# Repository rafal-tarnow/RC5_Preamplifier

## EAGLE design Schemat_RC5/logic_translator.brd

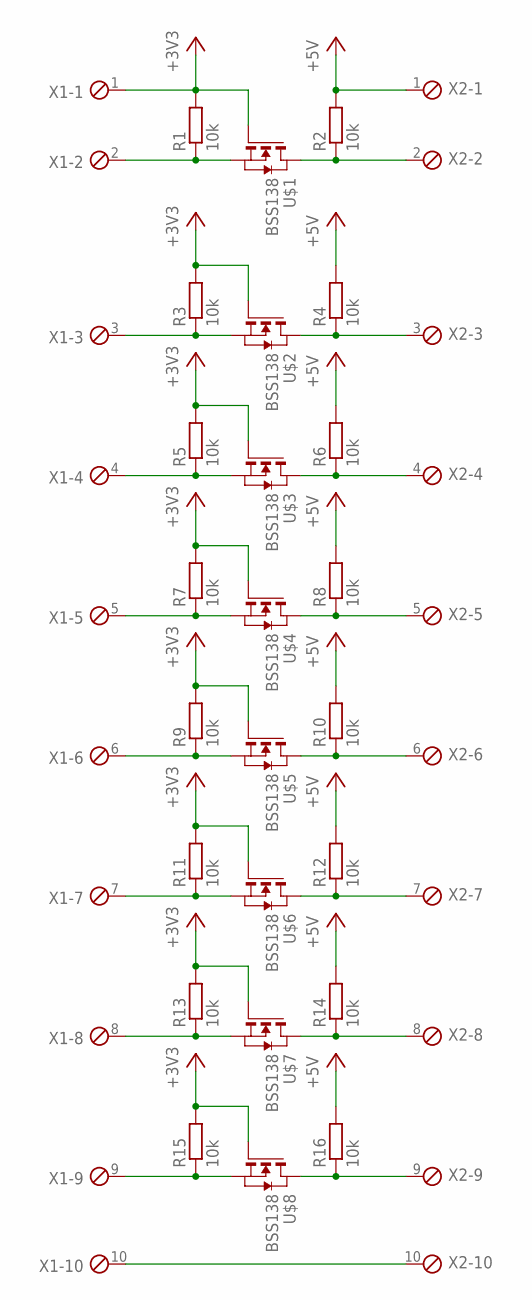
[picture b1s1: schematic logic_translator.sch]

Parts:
R1, R2, R3, R4, R5, R6, R7, R8, R9, R10, R11, R12, R13, R14, R15, R16: 10k; R1206
U$1, U$2, U$3, U$4, U$5, U$6, U$7, U$8: BSS138; SOT-23
X1, X2: MPT10; 10POL254

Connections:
+3V3: R1.2, R3.2, R5.2, R7.2, R9.2, R11.2, R13.2, R15.2, U$1.3 (G), U$2.3 (G), U$3.3 (G), U$4.3 (G), U$5.3 (G), U$6.3 (G), U$7.3 (G), U$8.3 (G), X1.1
+5V: R2.2, R4.2, R6.2, R8.2, R10.2, R12.2, R14.2, R16.2, X2.1
unnamed: R1.1, U$1.2 (S), X1.2
unnamed: R3.1, U$2.2 (S), X1.3
unnamed: R2.1, U$1.1 (D), X2.2
unnamed: R4.1, U$2.1 (D), X2.3
unnamed: R5.1, U$3.2 (S), X1.4
unnamed: R6.1, U$3.1 (D), X2.4
unnamed: R7.1, U$4.2 (S), X1.5
unnamed: R8.1, U$4.1 (D), X2.5
unnamed: R9.1, U$5.2 (S), X1.6
unnamed: R10.1, U$5.1 (D), X2.6
unnamed: R11.1, U$6.2 (S), X1.7
unnamed: R12.1, U$6.1 (D), X2.7
unnamed: R13.1, U$7.2 (S), X1.8
unnamed: R14.1, U$7.1 (D), X2.8
unnamed: R15.1, U$8.2 (S), X1.9
unnamed: R16.1, U$8.1 (D), X2.9
unnamed: X1.10, X2.10

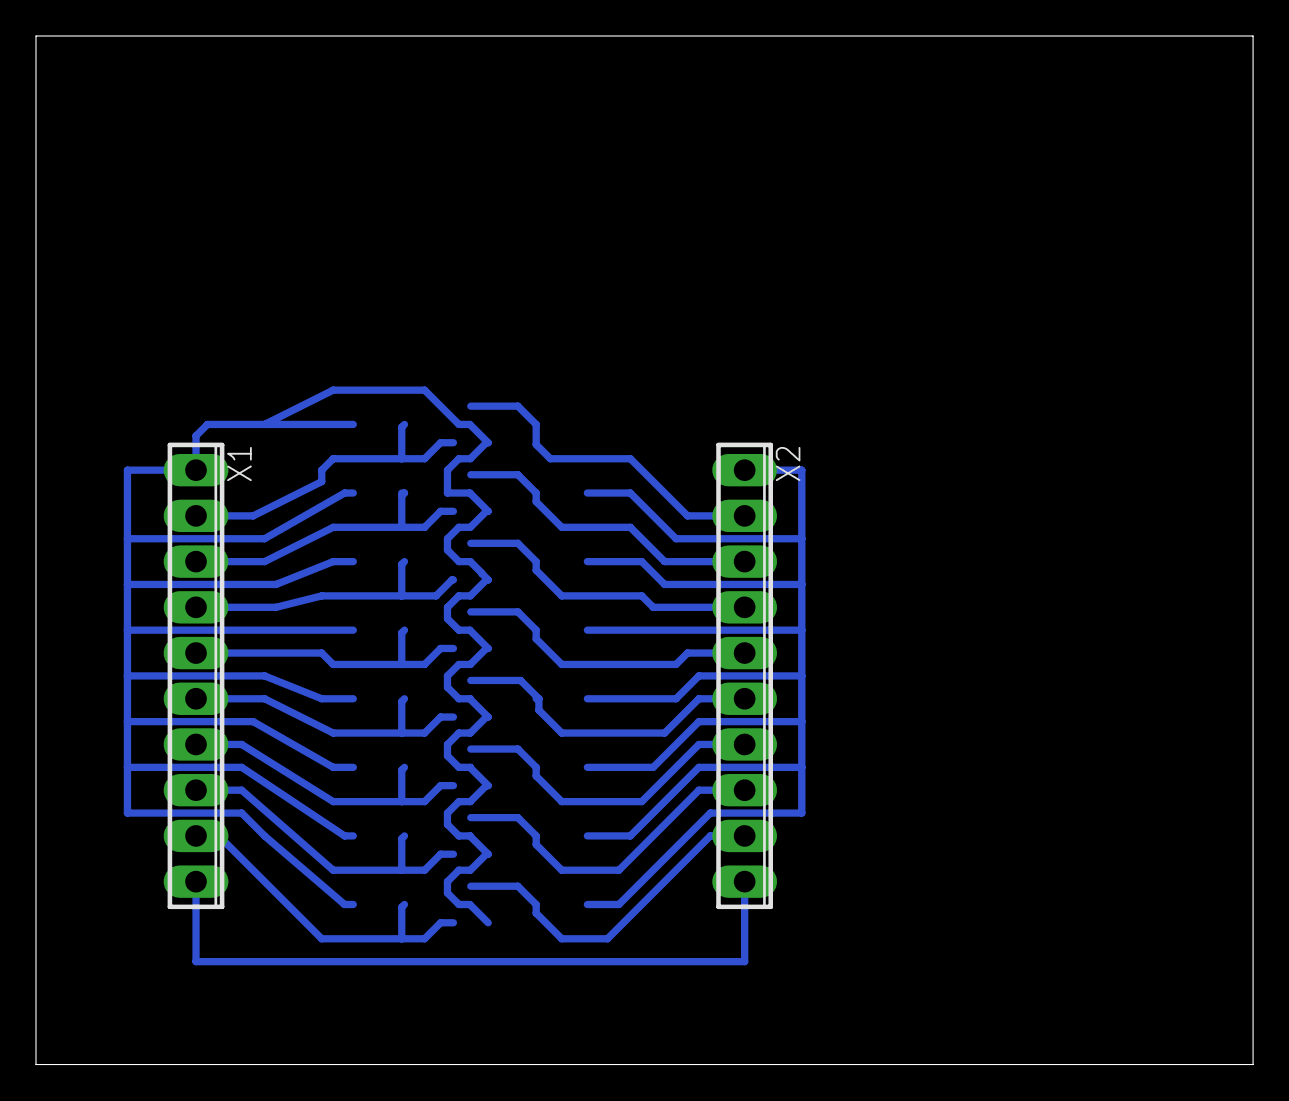
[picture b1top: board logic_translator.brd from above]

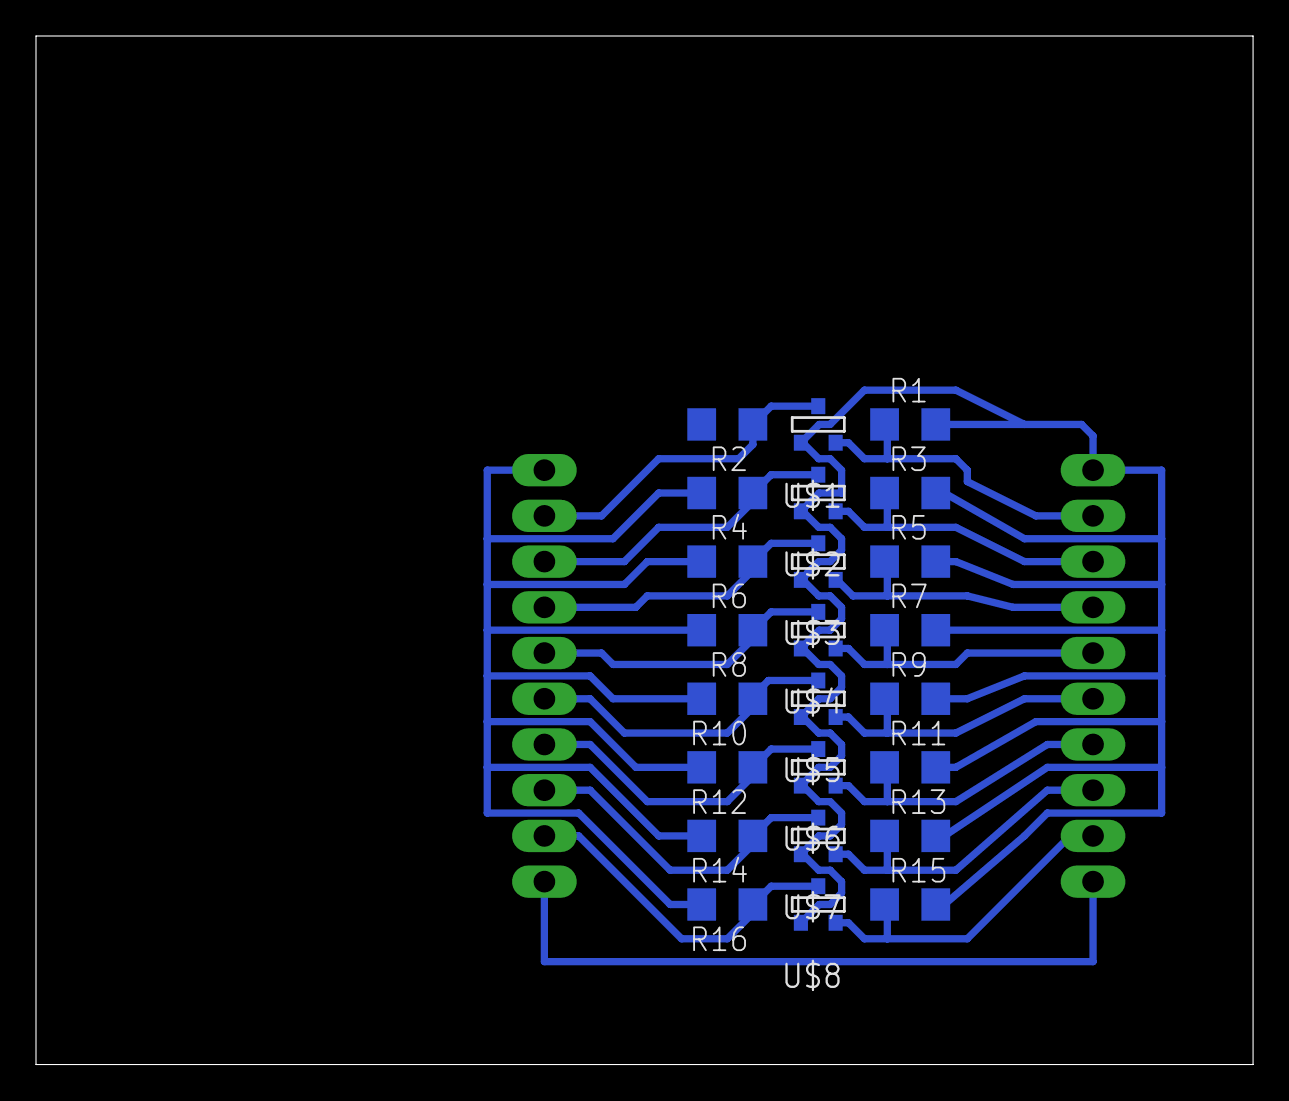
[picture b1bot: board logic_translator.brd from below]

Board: 2 copper layers, 67.6 x 57.1 mm, 26 parts (24 on the bottom side), 19 nets.

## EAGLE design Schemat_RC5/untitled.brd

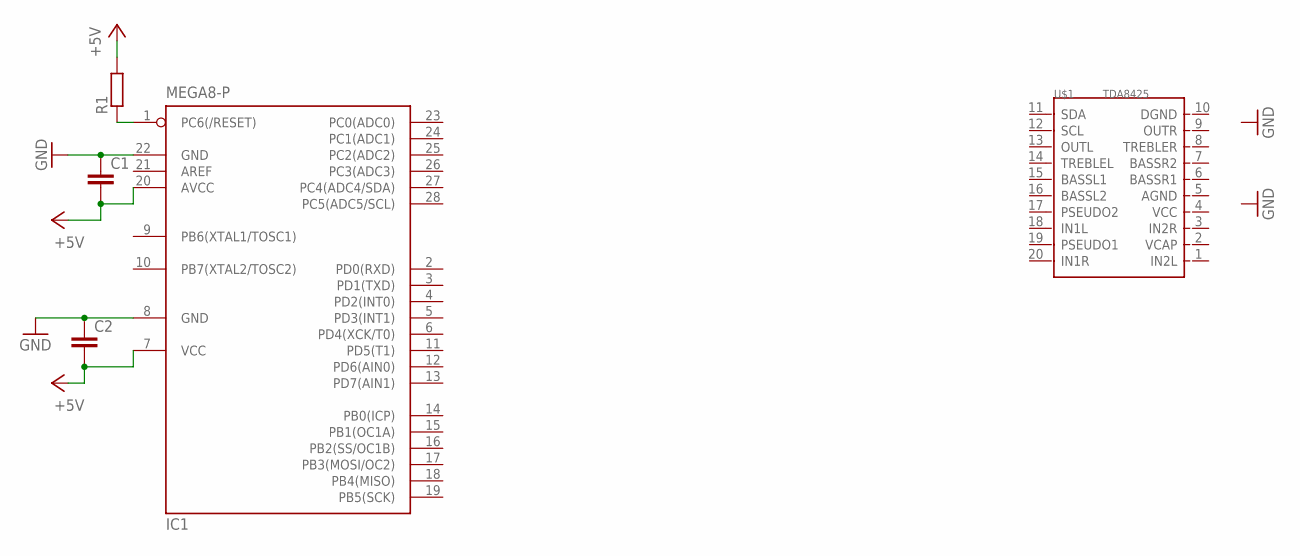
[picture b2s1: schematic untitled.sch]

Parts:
C1, C2: C-EUC0805; C0805
IC1: MEGA8-P; DIL28-3
R1: R-EU_R0805; R0805
U$1: TDA8425; DIP20-2.54-26.2X7.62MM

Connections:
+5V: C1.2, C2.2, IC1.7 (VCC), IC1.20 (AVCC), R1.2
GND: C1.1, C2.1, IC1.8 (GND), IC1.22 (GND)
unnamed: IC1.1 (PC6(/RESET)), R1.1

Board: 2 copper layers, 5 parts (0 on the bottom side), 3 nets, no tracks yet.

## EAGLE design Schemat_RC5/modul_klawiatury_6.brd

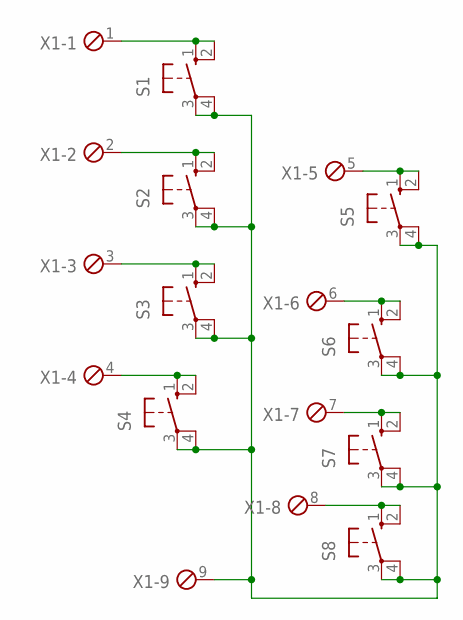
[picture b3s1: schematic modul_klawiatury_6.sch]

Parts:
S1, S2, S3, S4, S5, S6, S7, S8: 10-XX; B3F-10XX
X1: MPT9; 9POL254

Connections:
unnamed: S1.1 (S), S1.2 (S1), X1.1
unnamed: S2.1 (S), S2.2 (S1), X1.2
unnamed: S3.1 (S), S3.2 (S1), X1.3
unnamed: S4.1 (S), S4.2 (S1), X1.4
unnamed: S5.1 (S), S5.2 (S1), X1.5
unnamed: S6.1 (S), S6.2 (S1), X1.6
unnamed: S8.1 (S), S8.2 (S1), X1.8
unnamed: S7.1 (S), S7.2 (S1), X1.7
unnamed: S1.3, S1.4 (P1), S2.3, S2.4 (P1), S3.3, S3.4 (P1), S4.3, S4.4 (P1), S5.3, S5.4 (P1), S6.3, S6.4 (P1), S7.3, S7.4 (P1), S8.3, S8.4 (P1), X1.9

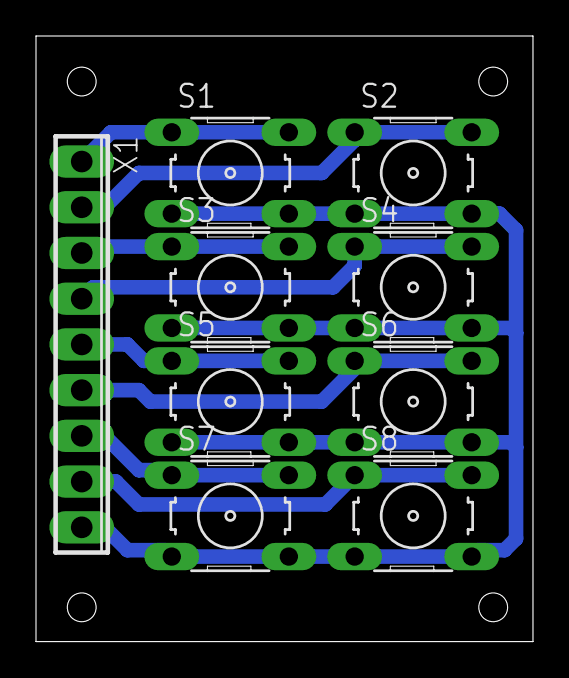
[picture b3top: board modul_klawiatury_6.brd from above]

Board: 2 copper layers, 27.6 x 33.6 mm, 9 parts (0 on the bottom side), 9 nets.

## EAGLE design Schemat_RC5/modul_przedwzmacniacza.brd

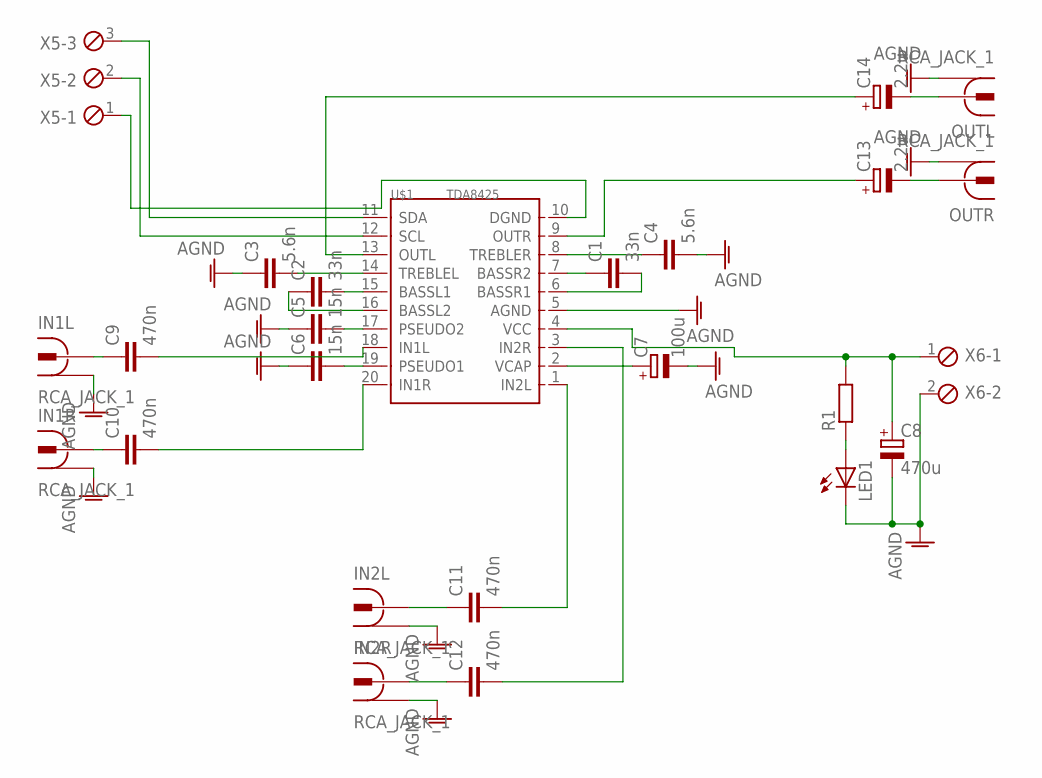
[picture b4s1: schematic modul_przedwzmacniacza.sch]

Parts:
C1, C2: 33n; C050-025X075
C3, C4: 5.6n; C050-030X075
C5, C6: 15n; C050-025X075
C7: 100u; E2,5-6
C8: 470u; E3,5-8
C9, C10, C11, C12: 470n; C050-045X075
C13, C14: 2.2u; E2-4
IN1L, IN1R, IN2L, IN2R: RCA_JACK_1; 736880-50
LED1: LED3MM
OUTL: RCA_JACK_1; 736880-50
OUTR: RCA_JACK_1; 736880-50
R1: R-EU_R1206; R1206
U$1: TDA8425; DIP20-2.54-26.2X7.62MM
X5: MPT3; 3POL254
X6: MPT2; 2POL254

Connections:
AGND: C3.1, C4.2, C5.1, C6.1, C7.-, C8.-, IN1L.1, IN1R.1, IN2L.1, IN2R.1, LED1.K (C), OUTL.1, OUTR.1, U$1.5 (AGND), X6.2
DGND: U$1.10 (DGND), X5.1
IN2R: C12.2, U$1.3 (IN2R)
unnamed: C11.2, U$1.1 (IN2L)
unnamed: C9.2, U$1.18 (IN1L)
unnamed: C10.2, U$1.20 (IN1R)
unnamed: C9.1, IN1L.2
unnamed: C10.1, IN1R.2
unnamed: C11.1, IN2L.2
unnamed: C1.1, U$1.7 (BASSR2)
unnamed: C1.2, U$1.6 (BASSR1)
unnamed: C2.2, U$1.15 (BASSL1)
unnamed: C2.1, U$1.16 (BASSL2)
unnamed: C3.2, U$1.14 (TREBLEL)
unnamed: C4.1, U$1.8 (TREBLER)
unnamed: C5.2, U$1.17 (PSEUDO2)
unnamed: C6.2, U$1.19 (PSEUDO1)
unnamed: C7.+, U$1.2 (VCAP)
unnamed: C12.1, IN2R.2
unnamed: C13.+, U$1.9 (OUTR)
unnamed: C13.-, OUTR.2
unnamed: C14.-, OUTL.2
unnamed: LED1.A, R1.1
OUTL: C14.+, U$1.13 (OUTL)
SCL: U$1.12 (SCL), X5.2
SDA: U$1.11 (SDA), X5.3
VCC: C8.+, R1.2, U$1.4 (VCC), X6.1

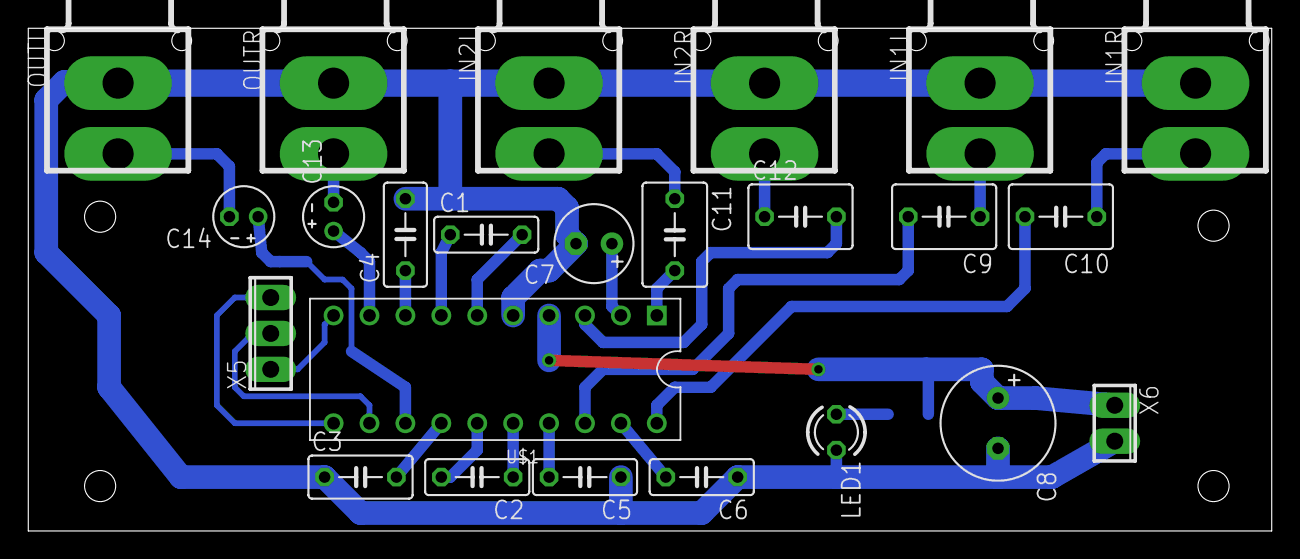
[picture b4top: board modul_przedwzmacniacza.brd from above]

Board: 2 copper layers, 87.9 x 35.5 mm, 25 parts (1 on the bottom side), 27 nets.

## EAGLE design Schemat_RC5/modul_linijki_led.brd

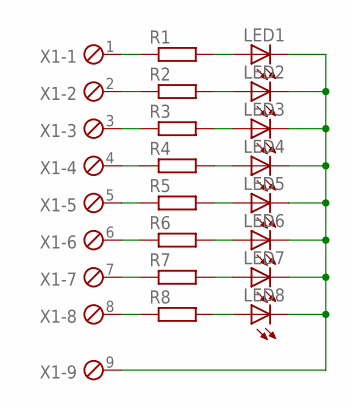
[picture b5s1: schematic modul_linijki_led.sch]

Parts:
LED1, LED2, LED3, LED4, LED5, LED6, LED7, LED8: LED3MM
R1, R2, R3, R4, R5, R6, R7, R8: R-EU_R0805; R0805
X1: MPT9; 9POL254

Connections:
unnamed: LED1.A, R1.2
unnamed: LED2.A, R2.2
unnamed: LED3.A, R3.2
unnamed: LED4.A, R4.2
unnamed: LED5.A, R5.2
unnamed: LED6.A, R6.2
unnamed: LED7.A, R7.2
unnamed: LED8.A, R8.2
unnamed: LED1.K (C), LED2.K (C), LED3.K (C), LED4.K (C), LED5.K (C), LED6.K (C), LED7.K (C), LED8.K (C), X1.9
unnamed: R1.1, X1.1
unnamed: R2.1, X1.2
unnamed: R3.1, X1.3
unnamed: R4.1, X1.4
unnamed: R5.1, X1.5
unnamed: R6.1, X1.6
unnamed: R7.1, X1.7
unnamed: R8.1, X1.8

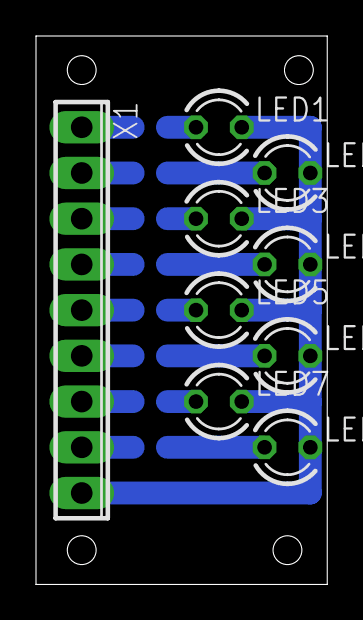
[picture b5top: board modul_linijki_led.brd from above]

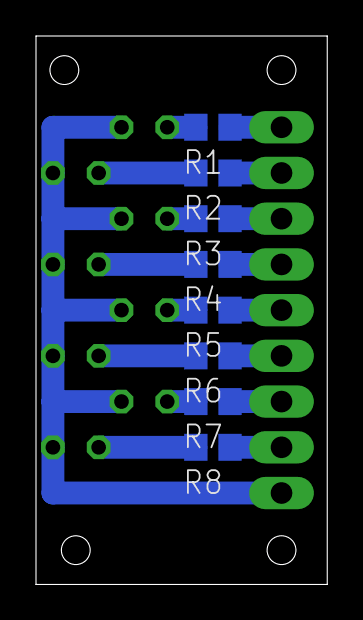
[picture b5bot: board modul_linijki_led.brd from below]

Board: 2 copper layers, 16.2 x 30.5 mm, 17 parts (8 on the bottom side), 17 nets.

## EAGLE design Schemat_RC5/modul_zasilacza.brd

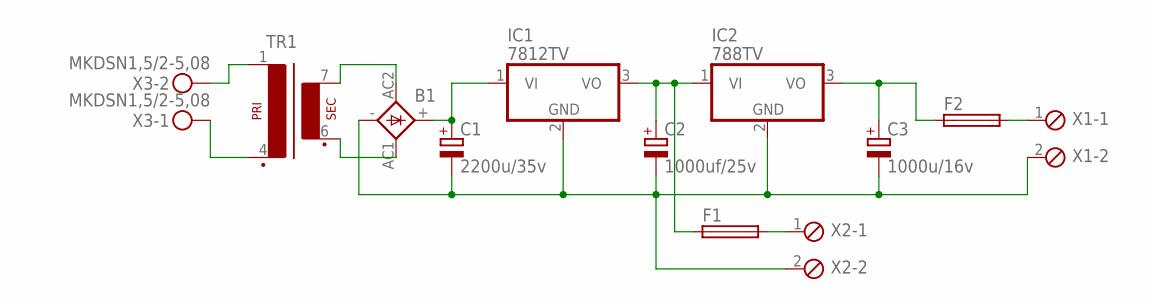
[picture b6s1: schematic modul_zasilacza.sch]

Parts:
B1: KBL
C1: 2200u/35v; E3,5-8
C2: 1000uf/25v; E3,5-8
C3: 1000u/16v; E3,5-8
F1, F2: GSH15
IC1: 7812TV; TO220V
IC2: 788TV; TO220V
TR1: EE20-1
X1, X2: MPT2; 2POL254
X3: MKDSN1,5/2-5,08

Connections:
unnamed: B1.+, C1.+, IC1.1 (VI)
unnamed: B1.AC1 (AC2), TR1.6 (S3)
unnamed: B1.AC2 (AC1), TR1.7 (S4)
unnamed: B1.-, C1.-, C2.-, C3.-, IC1.2 (GND), IC2.2 (GND), X1.2, X2.2
unnamed: C2.+, F1.1, IC1.3 (VO), IC2.1 (VI)
unnamed: F1.2, X2.1
unnamed: C3.+, F2.1, IC2.3 (VO)
unnamed: F2.2, X1.1
unnamed: TR1.1, X3.2
unnamed: TR1.4 (P2), X3.1

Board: 2 copper layers, 12 parts (0 on the bottom side), 10 nets, no tracks yet.

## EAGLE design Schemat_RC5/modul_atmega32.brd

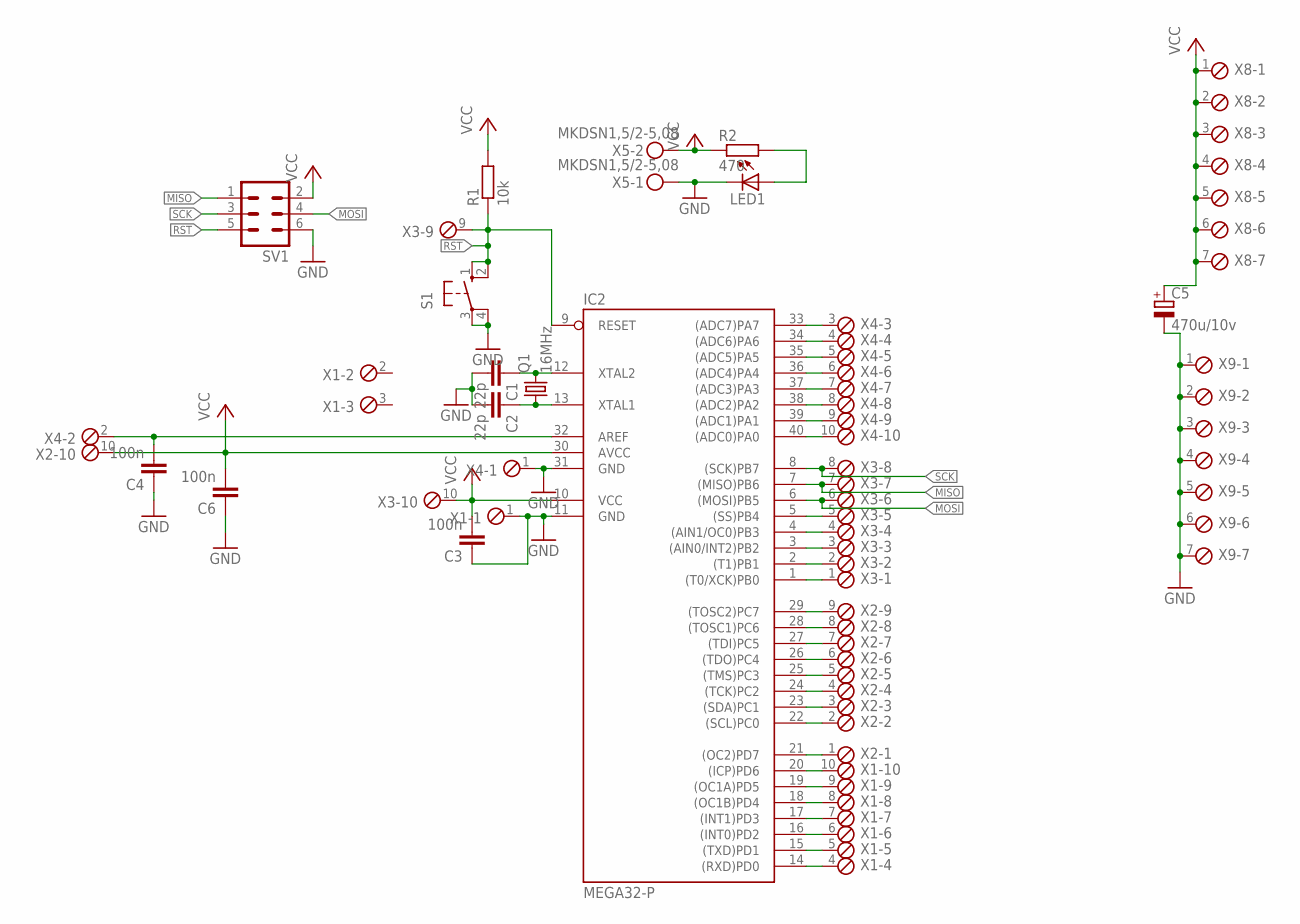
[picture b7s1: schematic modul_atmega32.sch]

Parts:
C1, C2: 22p; C0805K
C3, C4, C6: 100n; C1206
C5: 470u/10v; E5-8,5
IC2: MEGA32-P; DIL40
LED1: LED3MM
Q1: 16MHz; HC49UP
R1: 10k; R1206
R2: 470; R1206
S1: 10-XX; B3F-10XX
SV1: MA03-2
X1, X2, X3, X4: MPT10; 10POL254
X5: MKDSN1,5/2-5,08
X8, X9: MPT7; 7POL254

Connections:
AREF: C4.2, IC2.32 (AREF), X4.2
GND: C1.2, C2.2, C3.1, C4.1, C5.-, C6.1, IC2.11 (GND), IC2.31 (GND), LED1.K (C), S1.3, S1.4 (P1), SV1.6, X1.1, X4.1, X5.1, X9.1, X9.2, X9.3, X9.4, X9.5, X9.6, X9.7
MISO: IC2.7 ((MISO)PB6), SV1.1, X3.7
MOSI: IC2.6 ((MOSI)PB5), SV1.4, X3.6
unnamed: IC2.21 ((OC2)PD7), X2.1
unnamed: LED1.A, R2.2
unnamed: IC2.5 ((SS)PB4), X3.5
unnamed: IC2.4 ((AIN1/OC0)PB3), X3.4
unnamed: IC2.3 ((AIN0/INT2)PB2), X3.3
unnamed: IC2.2 ((T1)PB1), X3.2
unnamed: IC2.1 ((T0/XCK)PB0), X3.1
unnamed: IC2.14 ((RXD)PD0), X1.4
unnamed: IC2.15 ((TXD)PD1), X1.5
unnamed: IC2.16 ((INT0)PD2), X1.6
unnamed: IC2.17 ((INT1)PD3), X1.7
unnamed: IC2.18 ((OC1B)PD4), X1.8
unnamed: IC2.19 ((OC1A)PD5), X1.9
unnamed: IC2.20 ((ICP)PD6), X1.10
unnamed: C2.1, IC2.13 (XTAL1), Q1.1
unnamed: C1.1, IC2.12 (XTAL2), Q1.2
unnamed: IC2.29 ((TOSC2)PC7), X2.9
unnamed: IC2.28 ((TOSC1)PC6), X2.8
unnamed: IC2.27 ((TDI)PC5), X2.7
unnamed: IC2.26 ((TDO)PC4), X2.6
unnamed: IC2.25 ((TMS)PC3), X2.5
unnamed: IC2.24 ((TCK)PC2), X2.4
unnamed: IC2.23 ((SDA)PC1), X2.3
unnamed: IC2.22 ((SCL)PC0), X2.2
unnamed: IC2.33 ((ADC7)PA7), X4.3
unnamed: IC2.34 ((ADC6)PA6), X4.4
unnamed: IC2.35 ((ADC5)PA5), X4.5
unnamed: IC2.36 ((ADC4)PA4), X4.6
unnamed: IC2.37 ((ADC3)PA3), X4.7
unnamed: IC2.38 ((ADC2)PA2), X4.8
unnamed: IC2.39 ((ADC1)PA1), X4.9
unnamed: IC2.40 ((ADC0)PA0), X4.10
RST: IC2.9 (RESET), R1.1, S1.1 (S), S1.2 (S1), SV1.5, X3.9
SCK: IC2.8 ((SCK)PB7), SV1.3, X3.8
VCC: C3.2, C5.+, C6.2, IC2.10 (VCC), IC2.30 (AVCC), R1.2, R2.1, SV1.2, X2.10, X3.10, X5.2, X8.1, X8.2, X8.3, X8.4, X8.5, X8.6, X8.7

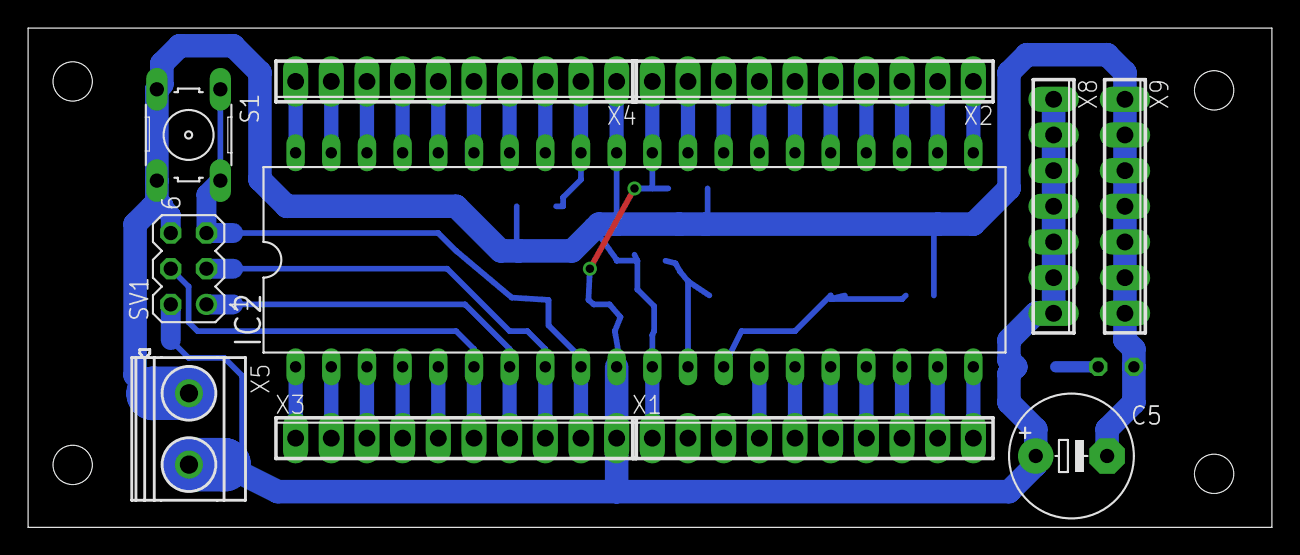
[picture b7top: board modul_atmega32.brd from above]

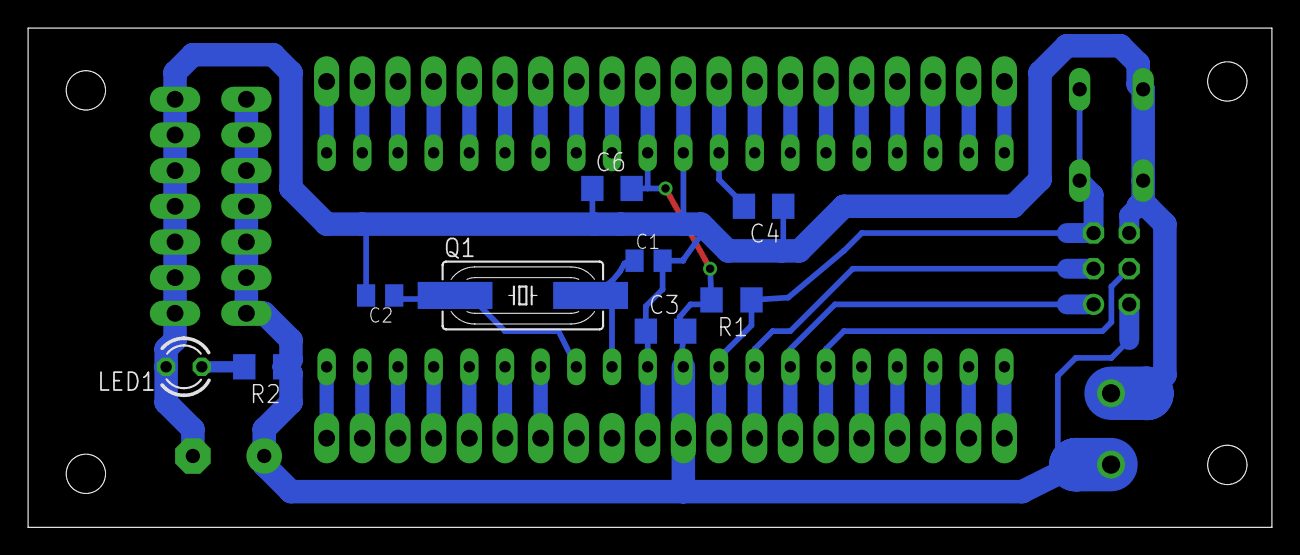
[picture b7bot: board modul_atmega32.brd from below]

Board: 2 copper layers, 88.6 x 35.5 mm, 20 parts (9 on the bottom side), 39 nets.

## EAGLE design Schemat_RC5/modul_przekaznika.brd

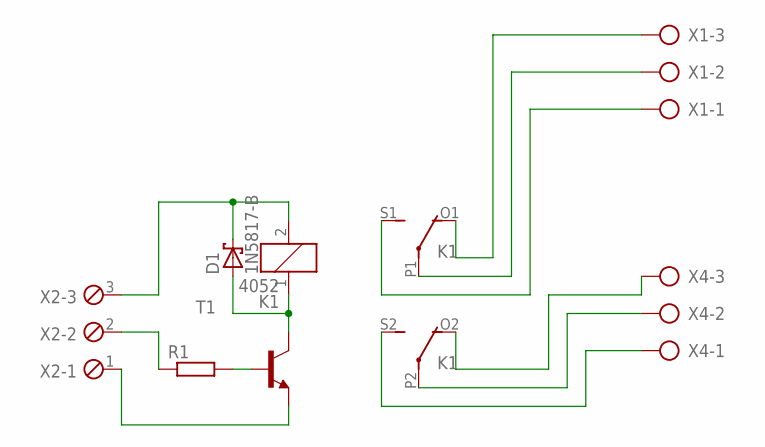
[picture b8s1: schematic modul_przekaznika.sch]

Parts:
D1: 1N5817-B; DO41-7.6
K1: 4052; F4052
R1: R-EU_M1206; M1206
T1: BC548-NPN-TO92-CBE; TO92-CBE
X1, X4: AK500/3
X2: MPT3; 3POL254

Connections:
unnamed: D1.A, K1.1, T1.C
unnamed: D1.C, K1.2, X2.3
unnamed: K1.S2 (S), X4.1
unnamed: K1.P2, X4.2
unnamed: K1.O2 (O), X4.3
unnamed: K1.S1 (S), X1.1
unnamed: K1.P1, X1.2
unnamed: K1.O1 (O), X1.3
unnamed: T1.E, X2.1
unnamed: R1.1, X2.2
unnamed: R1.2, T1.B

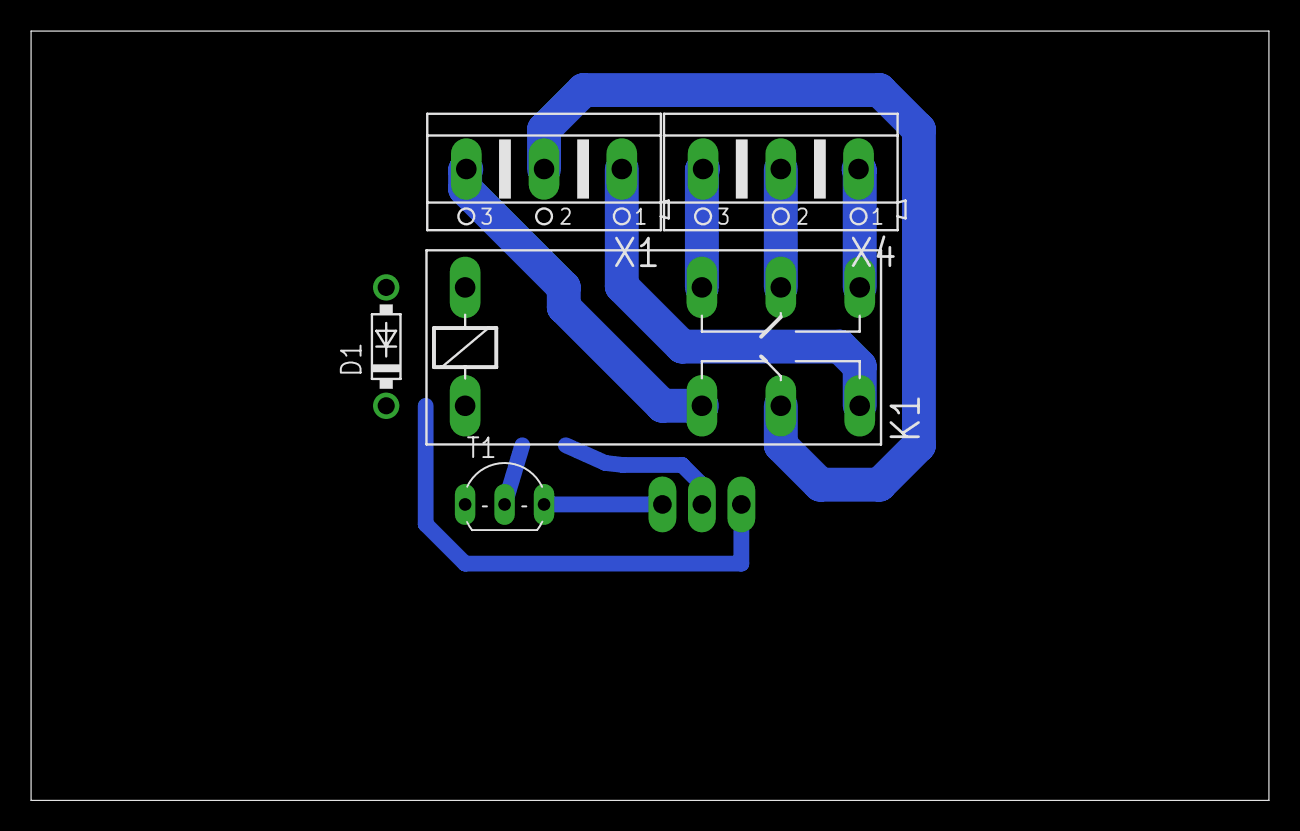
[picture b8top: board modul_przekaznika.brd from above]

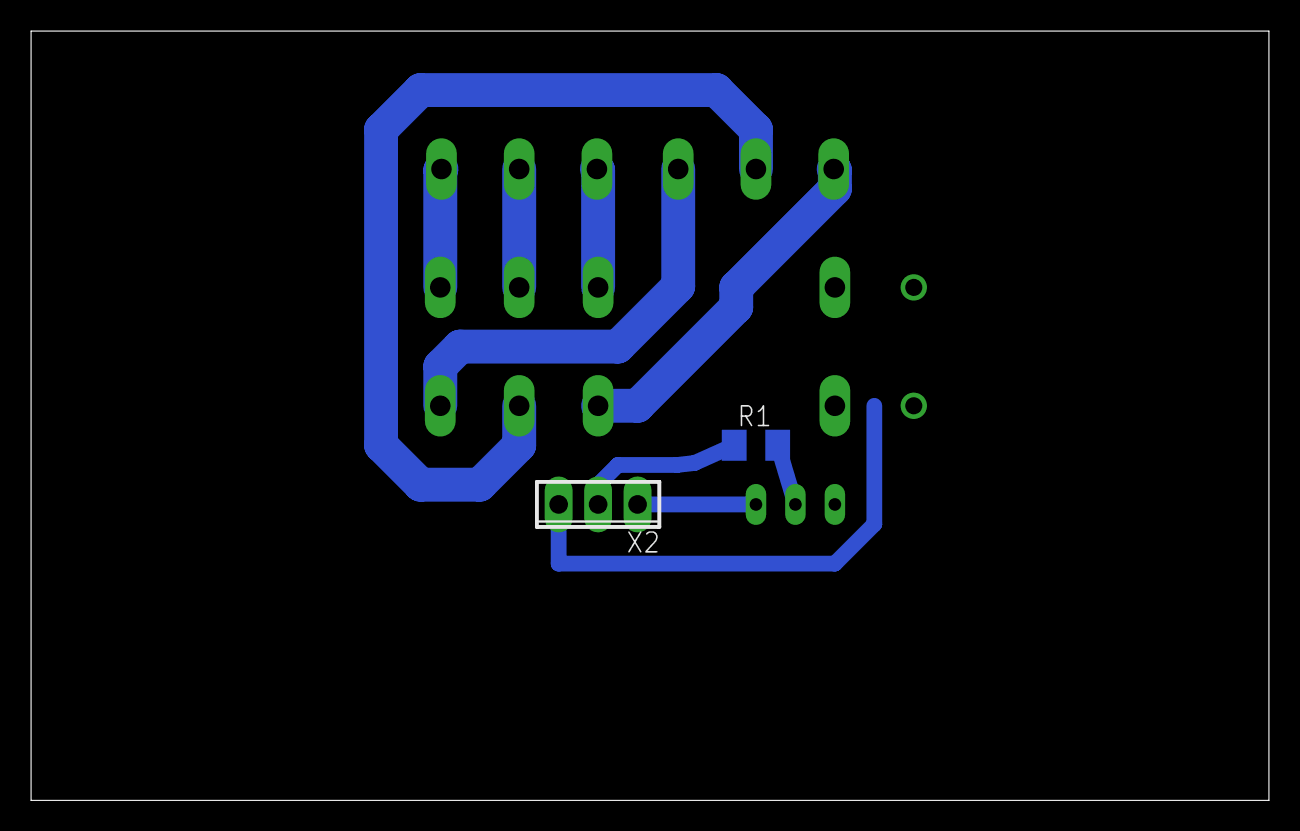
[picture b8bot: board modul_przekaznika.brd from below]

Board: 2 copper layers, 79.7 x 49.5 mm, 7 parts (2 on the bottom side), 11 nets.

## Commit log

2017-09-11 dodanie projektu avr
2017-09-11 dodanie schematu
